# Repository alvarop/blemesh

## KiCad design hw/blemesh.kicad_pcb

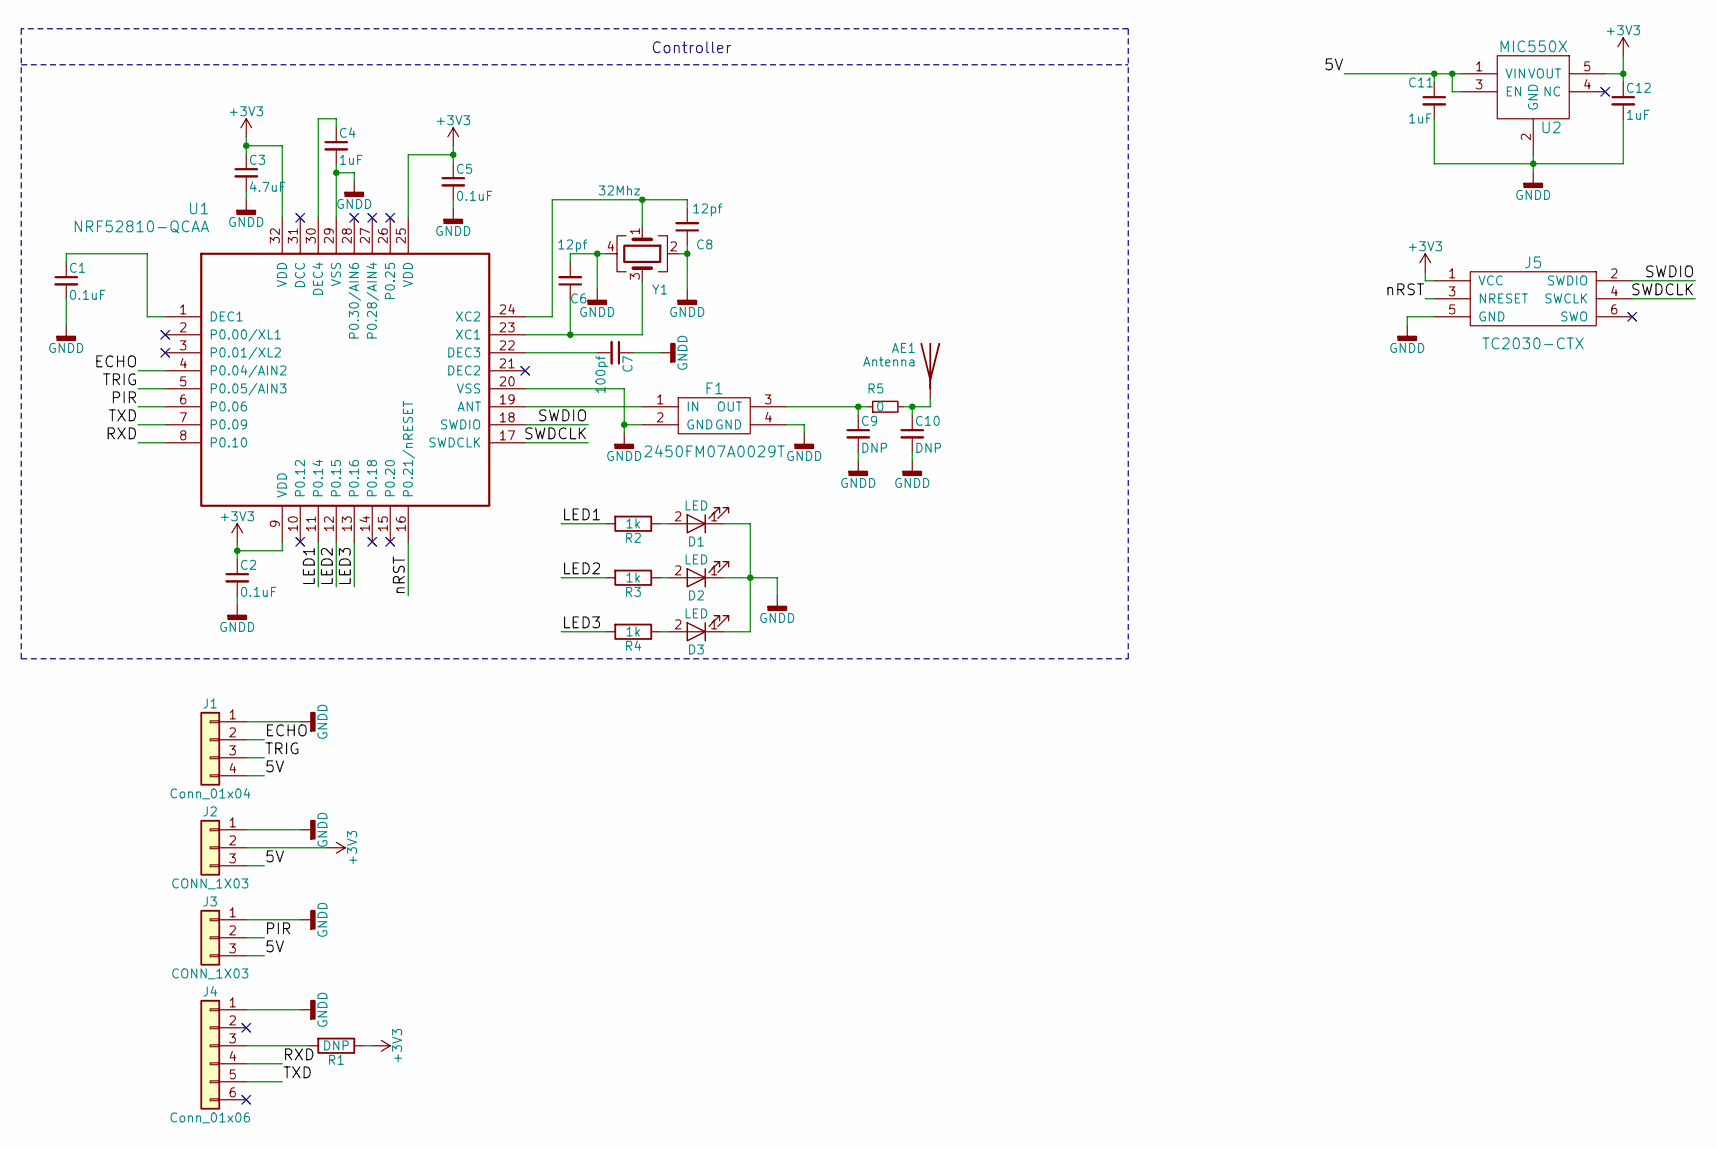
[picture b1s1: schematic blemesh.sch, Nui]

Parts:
AE1: Antenna; AMCA31-2R450G-S1F-T3
C1, C2, C5: 0.1uF; C_0402
C3: 4.7uF; C_0603
C4: 1uF; C_0402
C6, C8: 12pf; C_0402
C7: 100pf; C_0402
C9, C10: DNP; C_0402
C11, C12: 1uF; C_0603
D1, D2, D3: LED; LED_0402
F1: 2450FM07A0029T
J1: Conn_01x04; Pin_Header_Straight_1x04_Pitch2.54mm
J2, J3: CONN_1X03; Pin_Header_Straight_1x03_Pitch2.54mm
J4: Conn_01x06; Pin_Header_Straight_1x06_Pitch2.54mm
J5: TC2030-CTX; TC2030-NL
R1: DNP; R_0402
R2, R3, R4: 1k; R_0402
R5: 0; R_0402_NoSilk
U1: NRF52810-QCAA; NRF52810_QCAA_QFN32
U2: MIC550X; SOT-23(M5)
Y1: 32Mhz; Crystal_SMD_2016-4pin_2.0x1.6mm

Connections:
+3V3: C2.1, C3.1, C5.1, C12.1, J2.2, J5.1 (VCC), R1.1, U1.9 (VDD), U1.25 (VDD), U1.32 (VDD), U2.5 (VOUT)
/5V: C11.1, J1.4, J2.3, J3.3, U2.1 (VIN), U2.3 (EN)
/ECHO: J1.2, U1.4 (P0.04/AIN2)
/LED1: R2.2, U1.11 (P0.14)
/LED2: R3.2, U1.12 (P0.15)
/LED3: R4.2, U1.13 (P0.16)
/PIR: J3.2, U1.6 (P0.06)
/RXD: J4.4, U1.8 (P0.10)
/SWDCLK: J5.4 (SWCLK), U1.17 (SWDCLK)
/SWDIO: J5.2 (SWDIO), U1.18 (SWDIO)
/TRIG: J1.3, U1.5 (P0.05/AIN3)
/TXD: J4.5, U1.7 (P0.09)
/nRST: J5.3 (NRESET), U1.16 (P0.21/nRESET)
GNDD: C1.2, C2.2, C3.2, C4.2, C5.2, C6.2, C7.1, C8.1, C9.2, C10.2, C11.2, C12.2, D1.1 (K), D2.1 (K), D3.1 (K), F1.2 (GND), F1.4 (GND), J1.1, J2.1, J3.1, J4.1, J5.5 (GND), U1.20 (VSS), U1.29 (VSS), U2.2 (GND), Y1.2, Y1.4
unnamed: AE1.1, C10.1, R5.2
unnamed: C1.1, U1.1 (DEC1)
unnamed: C4.1, U1.30 (DEC4)
unnamed: C6.1, U1.23 (XC1), Y1.3
unnamed: C7.2, U1.22 (DEC3)
unnamed: C8.2, U1.24 (XC2), Y1.1
unnamed: C9.1, F1.3 (OUT), R5.1
unnamed: D1.2 (A), R2.1
unnamed: D2.2 (A), R3.1
unnamed: D3.2 (A), R4.1
unnamed: F1.1 (IN), U1.19 (ANT)
unnamed: J4.3, R1.2

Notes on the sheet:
Controller

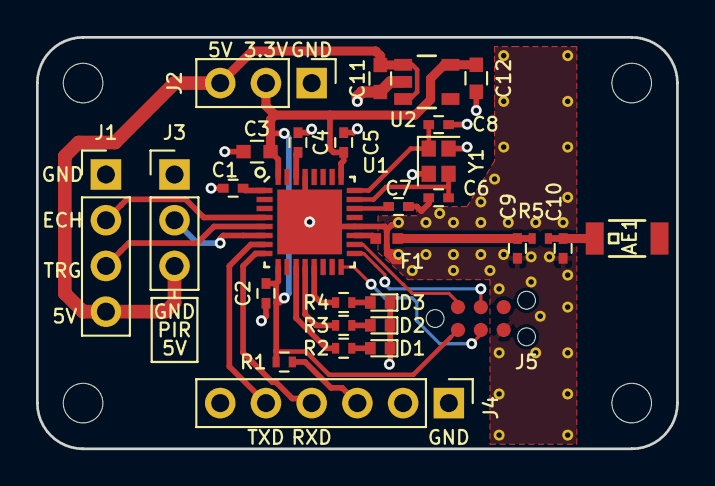
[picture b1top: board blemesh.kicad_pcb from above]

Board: 2 copper layers, 35.6 x 22.9 mm, 30 parts (0 on the bottom side), 26 nets.

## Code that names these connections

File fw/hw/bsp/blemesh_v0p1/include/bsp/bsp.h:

/*
 * Licensed to the Apache Software Foundation (ASF) under one
 * or more contributor license agreements.  See the NOTICE file
 * distributed with this work for additional information
 * regarding copyright ownership.  The ASF licenses this file
 * to you under the Apache License, Version 2.0 (the
 * "License"); you may not use this file except in compliance
 * with the License.  You may obtain a copy of the License at
 *
 *  http://www.apache.org/licenses/LICENSE-2.0
 *
 * Unless required by applicable law or agreed to in writing,
 * software distributed under the License is distributed on an
 * "AS IS" BASIS, WITHOUT WARRANTIES OR CONDITIONS OF ANY
 * KIND, either express or implied.  See the License for the
 * specific language governing permissions and limitations
 * under the License.
 */

#ifndef H_BSP_H
#define H_BSP_H

#include <inttypes.h>

#include <syscfg/syscfg.h>

#ifdef __cplusplus
extern "C" {
#endif

/* Define special stackos sections */
#define sec_data_core   __attribute__((section(".data.core")))
#define sec_bss_core    __attribute__((section(".bss.core")))
#define sec_bss_nz_core __attribute__((section(".bss.core.nz")))

/* More convenient section placement macros. */
#define bssnz_t         sec_bss_nz_core

extern uint8_t _ram_start;
#define RAM_SIZE        0x10000

/* LED pins */
#define LED_1_PIN (11)
#define LED_2_PIN (12)
#define LED_3_PIN (16)

#define ECHO_PIN (4)
#define TRIG_PIN (5)
#define PIR_PIN (6)

#ifdef __cplusplus
}
#endif

#endif  /* H_BSP_H */

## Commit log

2018-05-17 First commit. HW v0.1 and blinky fw
2018-05-17 Testing BLE functionality
2018-05-17 Updating bsp with NRF52810 defines
2018-05-17 Adding NRF52810 nrfx_config.h file to bsp
2018-05-18 Updating more NRF52810 defines for nrfx
2018-05-18 Stop tracking some files
2018-05-19 Trying out ws2812 LEDs
2018-05-19 Ultrasound working!
2018-05-20 Playing with the ultrasonic sensor
2018-05-28 Adding SPI-WS2812 LUT script
2018-05-28 Removed paste layer from tag connect footprint
2018-06-01 No need to use my mynewt repoo anymore
2019-01-21 Updating to work on latest mynewt
2019-01-21 Using ble beacons instead of mesh
    Because mesh is hard
2019-01-22 Fixed a few things
2020-04-18 transmit distance over beacon (old commit)
